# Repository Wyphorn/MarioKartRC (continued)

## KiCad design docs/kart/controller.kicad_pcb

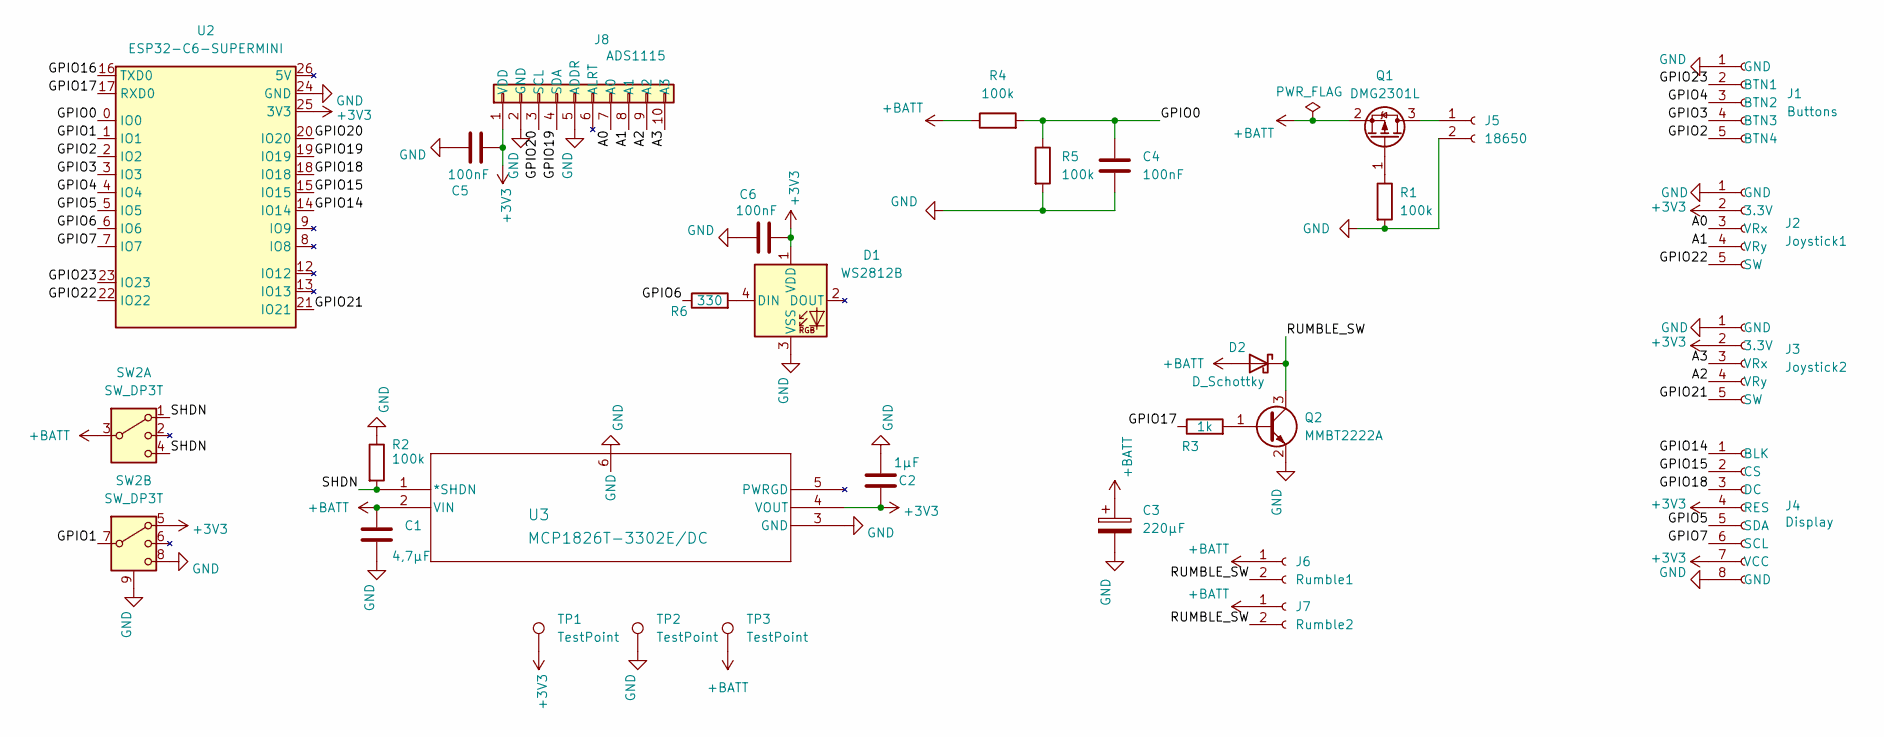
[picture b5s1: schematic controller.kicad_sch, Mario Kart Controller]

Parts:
C1: 4,7µF; C_0805_2012Metric_Pad1.18x1.45mm_HandSolder
C2: 1µF; C_0805_2012Metric_Pad1.18x1.45mm_HandSolder
C3: 220µF; CP_Elec_6.3x5.4
C4, C5, C6: 100nF; C_0805_2012Metric_Pad1.18x1.45mm_HandSolder
D1: WS2812B; LED_WS2812B_PLCC4_5.0x5.0mm_P3.2mm
D2: D_Schottky; D_SMA_Handsoldering
J1: Buttons; JST_XH_S5B-XH-A-1_1x05_P2.50mm_Horizontal
J2: Joystick1; JST_XH_S5B-XH-A-1_1x05_P2.50mm_Horizontal
J3: Joystick2; JST_XH_S5B-XH-A-1_1x05_P2.50mm_Horizontal
J4: Display; JST_XH_S8B-XH-A-1_1x08_P2.50mm_Horizontal
J5: 18650; SolderWire-1.5sqmm_1x02_P6mm_D1.7mm_OD3mm
J6: Rumble1; JST_XH_S2B-XH-A-1_1x02_P2.50mm_Horizontal
J7: Rumble2; JST_XH_S2B-XH-A-1_1x02_P2.50mm_Horizontal
J8: ADS1115; PinHeader_1x10_P2.54mm_Vertical
Q1: DMG2301L; SOT-23_Handsoldering
Q2: MMBT2222A; SOT-23_Handsoldering
R1, R2, R4, R5: 100k; R_0805_2012Metric_Pad1.20x1.40mm_HandSolder
R3: 1k; R_0805_2012Metric_Pad1.20x1.40mm_HandSolder
R6: 330; R_0805_2012Metric_Pad1.20x1.40mm_HandSolder
SW2: SW_DP3T; SW_Slide_2P3T_8pin_P2.0mm_MountingLugs
TP1, TP2, TP3: TestPoint; TestPoint_Pad_D2.0mm
U2: ESP32-C6-SUPERMINI; ESP32-C6-SuperMini_2x10_P2.54mm_Row15.24mm
U3: MCP1826T-3302E/DC; SOT-223_5MC_MCH

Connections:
+3V3: C2.1, C5.1, C6.1, D1.1 (VDD), J2.2 (3.3V), J3.2 (3.3V), J4.4 (RES), J4.7 (VCC), J8.1 (VDD), SW2.5, TP1.1, U2.25 (3V3), U3.4 (VOUT); also elsewhere on the board
+BATT: C1.1, C3.1, D2.2 (A), J6.1, J7.1, Q1.2 (S), R4.1, SW2.3, TP3.1, U3.2 (VIN); also elsewhere on the board
/A0: J2.3 (VRx), J8.7 (A0)
/A1: J2.4 (VRy), J8.8 (A1)
/A2: J3.4 (VRy), J8.9 (A2)
/A3: J3.3 (VRx), J8.10 (A3)
/GPIO0: C4.1, R4.2, R5.1, U2.0 (IO0)
/GPIO1: SW2.7, U2.1 (IO1)
/GPIO2: J1.5 (BTN4), U2.2 (IO2)
/GPIO3: J1.4 (BTN3), U2.3 (IO3)
/GPIO4: J1.3 (BTN2), U2.4 (IO4)
/GPIO5: J4.5 (SDA), U2.5 (IO5)
/GPIO6: R6.1, U2.6 (IO6)
/GPIO7: J4.6 (SCL), U2.7 (IO7)
/GPIO14: J4.1 (BLK), U2.14 (IO14)
/GPIO15: J4.2 (CS), U2.15 (IO15)
/GPIO16: U2.16 (TXD0)
/GPIO17: R3.1, U2.17 (RXD0)
/GPIO18: J4.3 (DC), U2.18 (IO18)
/GPIO19: J8.4 (SDA), U2.19 (IO19)
/GPIO20: J8.3 (SCL), U2.20 (IO20)
/GPIO21: J3.5 (SW), U2.21 (IO21)
/GPIO22: J2.5 (SW), U2.22 (IO22)
/GPIO23: J1.2 (BTN1), U2.23 (IO23)
/RUMBLE_SW: D2.1 (K), J6.2, J7.2, Q2.3 (C)
/SHDN: R2.2, SW2.1, SW2.4, U3.1 (*SHDN)
GND: C1.2, C2.2, C3.2, C4.2, C5.2, C6.2, D1.3 (VSS), J1.1 (GND), J2.1 (GND), J3.1 (GND), J4.8 (GND), J5.2, J8.2 (GND), J8.5 (ADDR), Q2.2 (E), R1.2, R2.1, R5.2, SW2.8, SW2.9 (GND), TP2.1, U2.24 (GND), U3.3 (GND), U3.6 (GND); also elsewhere on the board
unnamed: D1.4 (DIN), R6.2
unnamed: J5.1, Q1.3 (D)
unnamed: Q1.1 (G), R1.1
unnamed: Q2.1 (B), R3.2

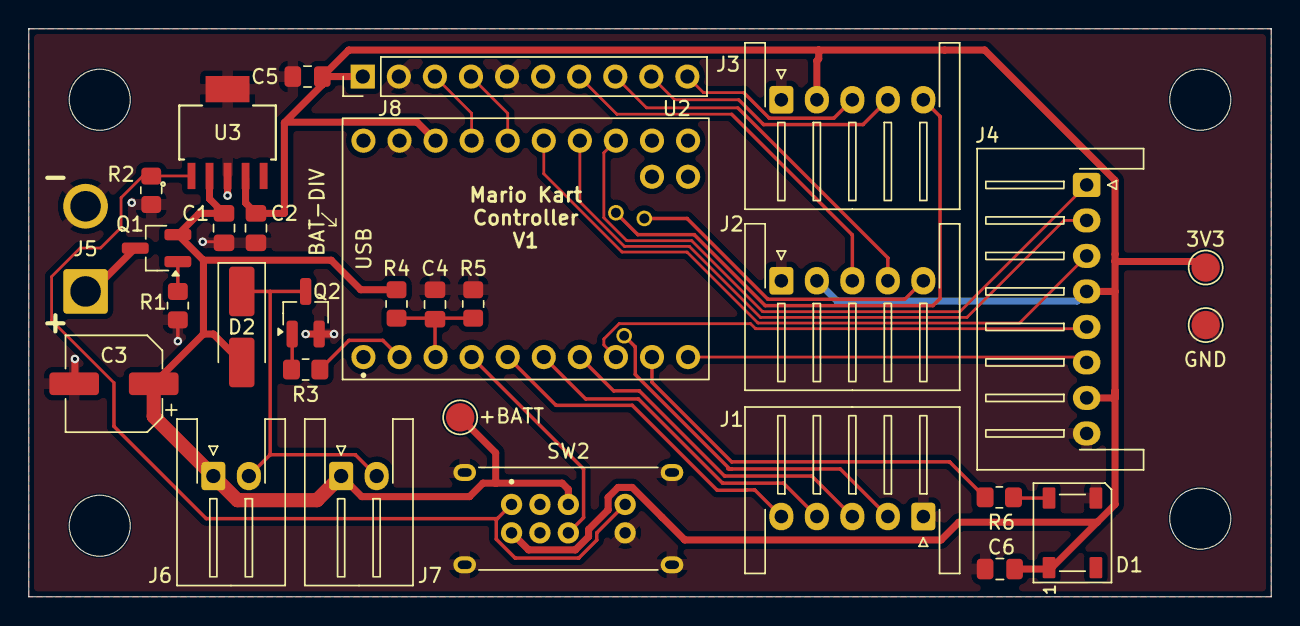
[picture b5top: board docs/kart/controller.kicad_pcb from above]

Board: 2 copper layers, 87.5 x 40.0 mm, 30 parts (0 on the bottom side), 30 nets.

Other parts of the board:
3V3: TestPoint; TestPoint_Pad_D2.0mm
+BATT: TestPoint; TestPoint_Pad_D2.0mm
GND: TestPoint; TestPoint_Pad_D2.0mm

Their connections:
+3V3: 3V3.1 (1_1); also elsewhere on the board
+BATT: +BATT.1 (1_1); also elsewhere on the board
GND: GND.1 (1_1); also elsewhere on the board

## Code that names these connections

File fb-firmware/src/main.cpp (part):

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
// --- Pins (ESP32-C6-SuperMini, Repin 2026-09-06) ---
// Tabu: GPIO12/13 (USB D-/D+), GPIO8/9 (RGB-LED / BOOT-Strap),
//       GPIO16/17 (UART0 — TXD0 wird vom Boot-ROM aktiv getrieben; auf V2
//       traegt GPIO16 bewusst die Status-LED, ein reiner Ausgang).
// ADC1 liegt nur auf GPIO0–6, der Batterie-Monitor muss dorthin.
#define PIN_BAT_ADC      0   // ADC1_0, externer Teiler 100k/100k
#define PIN_MODE         1   // fest an 3.3V/GND — darf kein UART0-TX sein
#define PIN_BTN_RED      2
#define PIN_BTN_BLUE     3
#define PIN_BTN_GREEN    4
// FB-Board V2 (2026-10-06): Gelb von inneren Pad 23 an die Hauptleiste
// (GPIO5), Display-MOSI auf GPIO6, Status-LED auf GPIO16 (UART0 TX — der
// Boot-ROM gibt dort ~17 ms sein Startprotokoll aus, die LED blitzt beim
// Einschalten evtl. kurz in einer Zufallsfarbe, bis setup() sie setzt).
// Kein fliegender Draht mehr. env fb_v2 setzt -DFB_REV=2.
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#define PIN_TFT_SCK      7   // FSPI SCK — IO_MUX, volle Taktrate
#define PIN_TFT_BL      14   // Backlight, PWM-gedimmt
#define PIN_TFT_CS      15
// GPIO16 = UART0 TXD0 — im Layout nicht erreichbar, bleibt frei.
#define PIN_RUMBLE      17   // LEDC. GPIO17 = UART0 RXD0 — der ROM liest den Pin
                             // nur, treibt ihn nie. Kein Motorzappeln beim Boot.
#define PIN_TFT_DC      18
#define PIN_I2C_SDA     19
#define PIN_I2C_SCL     20
// GPIO21-23 liegen auf den inneren Pads des SuperMini, nicht an den
// Hauptleisten — dort ist je ein Draht noetig.
#define PIN_BTN_STICK_R 21   // reserviert, bewusst ohne Funktion
#define PIN_BTN_STICK_L 22   // reserviert, bewusst ohne Funktion
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// lassen und den Rumble abschalten. Analog zu gBatWired in der Auto-Firmware.
// Auf true setzen, sobald der Teiler dran ist. Verdrahtet seit 2026-09-25.
#if defined(MK_TEST_BARE) || defined(MK_TEST_USB_POWER)
// Testbuilds: fb_bare (nacktes C6, GPIO0 haengt in der Luft) und fb_usbpower
// (Platine ohne Akku, Versorgung per USB — ueber den LDO rueckgespeist liegt
// das Akku-Netz bei ~2.7V). In beiden Faellen wuerde der Tiefentladeschutz
// sonst auf falsche Werte reagieren.
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
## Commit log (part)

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2026-05-16 Initial commit: FB PoC Projektstruktur + CLAUDE.md
2026-05-16 Add README with hardware docs and project status
